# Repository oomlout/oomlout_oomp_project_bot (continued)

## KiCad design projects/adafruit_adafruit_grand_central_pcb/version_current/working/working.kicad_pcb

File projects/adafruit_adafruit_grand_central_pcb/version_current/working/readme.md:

# OOMP Project  
## Adafruit-Grand-Central-PCB  by adafruit  
  
oomp key: oomp_projects_flat_adafruit_adafruit_grand_central_pcb  
(snippet of original readme)  
  
-- Adafruit Grand Central M4 Express featuring the SAMD51 PCB  
  
<a href="http://www.adafruit.com/products/4064"><br/>  
Click here to purchase one from the Adafruit shop</a>  
  
PCB files for the Adafruit Grand Central M4 Express featuring the SAMD51. Format is EagleCAD schematic and board layout  
* https://www.adafruit.com/product/4064  
  
--- Description  
  
We're selling out fast but making more all the time! Sign up to be notified when it's in the store!  
  
Are you ready? Really ready? Cause here comes the **Adafruit Grand Central** featuring the **Microchip ATSAMD51**. This dev board is so big, it's not named after a Metro train, it's a whole freakin' station!  
  
This board is like a freight train, with its 120MHz Cortex M4 with floating point support. Your code will zig and zag and zoom, and with a bunch of extra peripherals for support, this will for sure be your favorite new chipset.  
  
The Grand Central is the first SAMD board that has enough pins to make it in the form of the Arduino Mega - with a massive number of pins, tons of analog inputs, dual DAC output, 8 MBytes of QSPI flash, SD card socket, and a NeoPixel.  
  
To start off our ATSAMD51 journey we are going large with the Mega shape and pinout you know and love. The front half has the same shape and pinout as our Metro's, so it is compatible with all our shields. It's got analog pins where you expect, and SPI/UART/I2C hardware support in the same spot as the Metro 328 and M0. But!  
  full source readme at [readme_src.md](readme_src.md)  
  
source repo at: [https://github.com/adafruit/Adafruit-Grand-Central-PCB](https://github.com/adafruit/Adafruit-Grand-Central-PCB)  
## Board  

## Schematic  

[schematic pdf](working_schematic.pdf)  
## Images

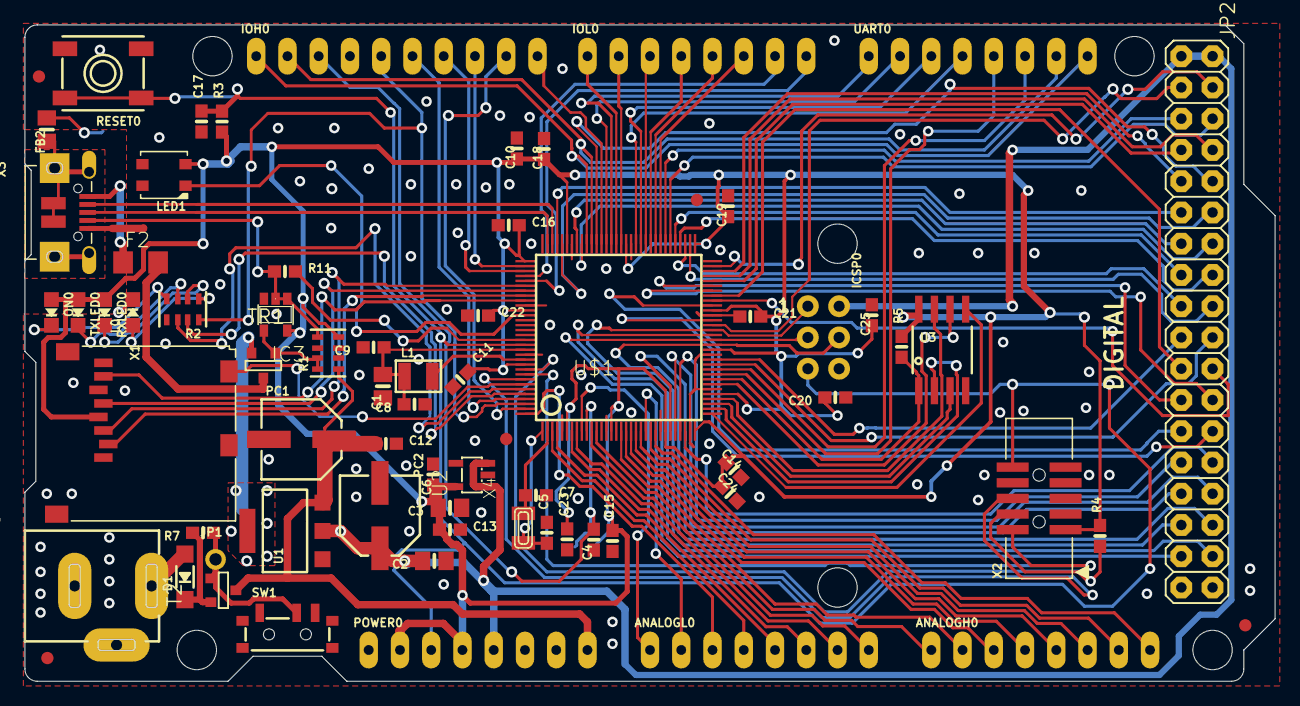
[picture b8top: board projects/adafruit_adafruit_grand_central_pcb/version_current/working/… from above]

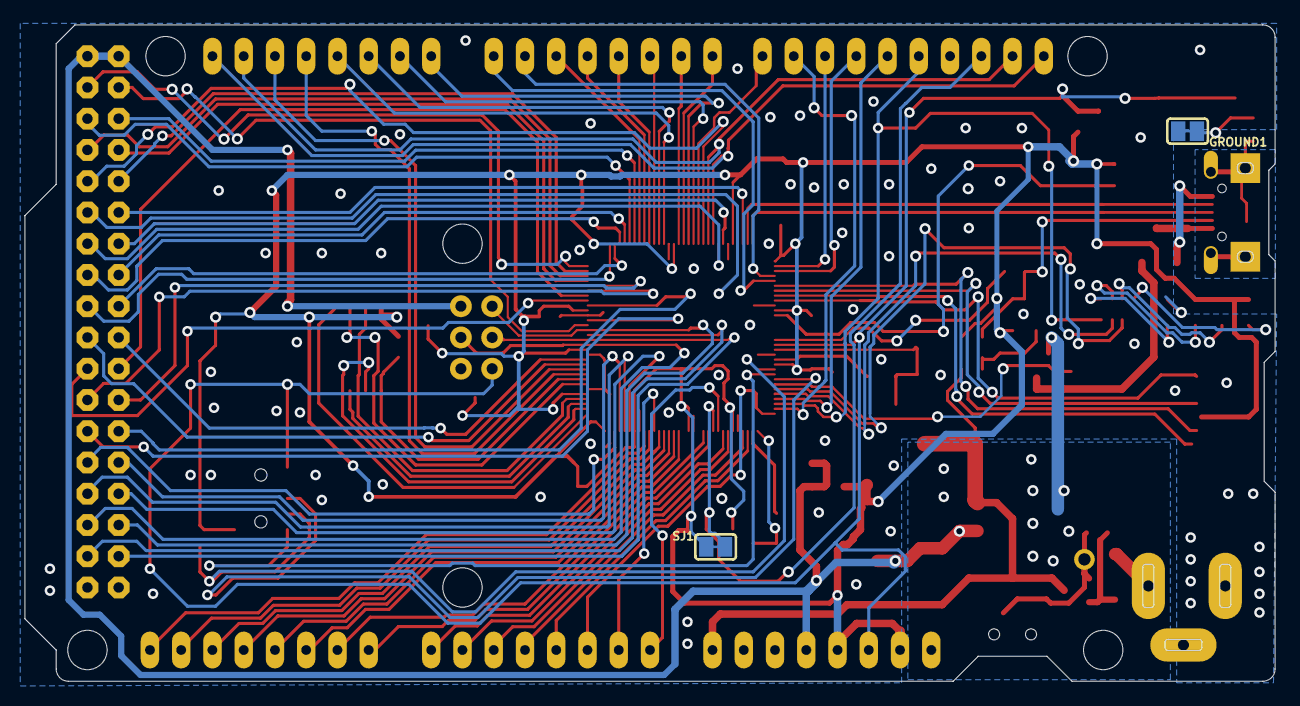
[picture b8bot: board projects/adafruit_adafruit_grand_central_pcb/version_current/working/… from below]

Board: 2 copper layers, 101.6 x 53.3 mm, 81 parts (3 on the bottom side), 113 nets.

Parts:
@HOLE0, @HOLE1, @HOLE2, @HOLE3, @HOLE4, @HOLE5: (no value)
ANALOGH0: 20610; 1X08_OVALWAVE
ANALOGL0: 20610; 1X08_OVALWAVE
C1, C2, C3: 10uF; 0805-NO
C4, C6, C8, C10, C11, C14, C15, C16, C18, C19, C20, C21, C22, C23, C24, C25: .1u; 0603-NO
C5, C7: 22pF; 0603-NO
C9: 1uF; 0603-NO
C12, C13, C17: 0.1uF; 0603-NO
D1: MBR120; SOD-123
F2: 500mA; R1206
FB2: FERRITE; 0805-NO
FD1, FD2, FD3, FD4, FD5: FIDUCIAL_1MM
GROUND1: SOLDERJUMPER_CLOSEDWIRE
IC3: 74LVC1G125D; SOT23-5
ICSP0: 3x2 M; 2X03_ROUND_70MIL
IOH0: 20611; 1X10_OVALWAVE
IOL0: 20610; 1X08_OVALWAVE
JP1: 1X01_ROUND
JP2: 2X18_THICKWAVE
L0: RED; CHIPLED_0805_NOOUTLINE
L1: 10uH; INDUCTOR_1007
LED1: WS2812B3535; LED3535
ON0: GREEN; CHIPLED_0805_NOOUTLINE
PC1: 47uF/25V; PANASONIC_D
PC2: 47uF+/6.3V+; PANASONIC_D
POWER0: 20610; 1X08_OVALWAVE
R1: 100K; RESPACK_4X0603
R2: 1K; RESPACK_4X0603
R3, R5, R7: 10K; 0603-NO
R4: 1K; 0603-NO
R11: 330R; 0603-NO
RESET0: EVQQ 6mm; EVQ-Q2_SMALLER
RXLED0: YELLOW; CHIPLED_0805_NOOUTLINE
SJ1: AREF_3V; SOLDERJUMPER_CLOSEDWIRE
SW1: SPDT_SMT_SSSS811101
T2: DMP3098L-7; SOT-23
TR1: DMP3098L-7; SOT-23
TXLED0: YELLOW; CHIPLED_0805_NOOUTLINE
U1: NCP1117ST50T3G; SOT223-R
U2: AP2112K-3.3; SOT23-DBV
U3: GD25Q64; SOIC8_208MIL
U$1: SAMD51PXXA; SQFP-S-14X14-128
U$23: GRANDCENTRAL_REVB-BOT
U$30: GRANDCENTRAL_REVB_TOP
UART0: 20610; 1X08_OVALWAVE
X1: microsd; MICROSD
X2: 2x5 0.05" SWD; 2X05_1.27MM_BOX_POSTS
X3: 20329; 4UCONN_20329_V2
X4: 32.768; XTAL3215
X5: 2.1mm; DCJACK_2MM_PTH

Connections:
3.3V: C3.2, C6.2, C10.2, C11.2, C13.1, C14.2, C15.2, C16.2, C18.2, C19.2, C20.2, C21.2, C22.2, C23.2, C24.2, C25.2, IC3.5, LED1.2, ON0.A, POWER0.2, POWER0.4, R1.4, R3.1, R4.2, R5.2, RXLED0.A, SJ1.1, TXLED0.A, U2.5, U3.8, U$1.6, U$1.15, U$1.26, U$1.32, U$1.37, U$1.46, U$1.54, U$1.65, U$1.79, U$1.91, U$1.97, U$1.107, U$1.118, X1.4, X2.1
+5V: C2.2, ICSP0.2, JP2.1, JP2.2, PC2.+, POWER0.5, TR1.2, U1.2, U1.4, U2.1, U2.3
A0: ANALOGL0.1, U$1.9
A1: ANALOGL0.2, U$1.22
A2: ANALOGL0.3, U$1.128
A3: ANALOGL0.4, U$1.3
A4: ANALOGL0.5, U$1.4
A5: ANALOGL0.6, U$1.7
A6: ANALOGL0.7, U$1.8
A7: ANALOGL0.8, U$1.11
A8: ANALOGH0.1, U$1.12
A9: ANALOGH0.2, U$1.17
A10: ANALOGH0.3, U$1.18
A11: ANALOGH0.4, U$1.19
A12: ANALOGH0.5, U$1.20
A13: ANALOGH0.6, U$1.21
A14: ANALOGH0.7, U$1.23
A15: ANALOGH0.8, U$1.24
AREF: C4.1, IOH0.3, SJ1.2, U$1.10
D0: IOL0.8, U$1.101
D1: IOL0.7, U$1.100
D2: IOL0.6, U$1.72
D3: IOL0.5, U$1.73
D4: IOL0.4, U$1.74
D5: IOL0.3, U$1.75
D6: IOL0.2, U$1.80
D7: IOL0.1, U$1.81
D8: IOH0.10, U$1.84
D9: IOH0.9, U$1.127
D10: IOH0.8, U$1.98
D11: IOH0.7, U$1.99
D12: IOH0.6, U$1.125
D13: IOH0.5, R2.8, U$1.126
D22: JP2.3, U$1.51
D23: JP2.4, U$1.63
D44: JP2.25, U$1.55
D45: JP2.26, U$1.52
D46: JP2.27, U$1.29
D47: JP2.28, U$1.30
D48: JP2.29, U$1.27
D49: JP2.30, U$1.28
D+: U$1.95, X3.D+
D-: U$1.94, X3.D-
FLASH_CS: R5.1, U3.1, U$1.40
FLASH_IO0: U3.5, U$1.33
FLASH_IO1: U3.2, U$1.34
FLASH_IO2: U3.3, U$1.35
FLASH_IO3: U3.7, U$1.36
FLASH_SCK: U3.6, U$1.39
GND: C1.2, C2.1, C3.1, C4.2, C5.2, C6.1, C7.2, C8.1, C9.2, C10.1, C11.1, C12.2, C13.2, C14.1, C15.1, C16.1, C17.1, C18.1, C19.1, C20.1, C21.1, C22.1, C23.1, C24.1, C25.1, GROUND1.2, IC3.3, ICSP0.6, IOH0.4, JP2.35, JP2.36, L0.C, LED1.4, PC1.-, PC2.-, POWER0.6, POWER0.7, R1.2, R2.5, RESET0.A, RESET0.A', SW1.A, U1.1, U2.2, U3.4, U$1.5, U$1.14, U$1.25, U$1.31, U$1.38, U$1.45, U$1.53, U$1.64, U$1.78, U$1.90, U$1.96, U$1.106, U$1.116, X1.6, X1.MT1, X1.MT2, X2.3, X2.5, X3.GND, X5.GND, X5.GNDBREAK
MISO: ICSP0.1, JP2.31, U$1.50
MOSI: ICSP0.4, JP2.32, U$1.47
unnamed: L0.A, R2.1
unnamed: FB2.1, GROUND1.1
unnamed: ON0.C, R2.4
unnamed: L1.P$2, U$1.117
unnamed: R2.2, RXLED0.C
unnamed: R2.3, TXLED0.C
unnamed: C5.1, U$1.1, X4.P$1
unnamed: IC3.1, IC3.2, R1.5, R11.1, X3.ID
unnamed: IC3.4, R1.7, R1.8, TR1.3
unnamed: C7.1, U$1.2, X4.P$2
unnamed: D1.C, R7.2, T2.2
NEOPIX: LED1.1, U$1.108
PCC_CLK: JP2.9, U$1.62
PCC_D0: JP2.18, U$1.66
PCC_D1: JP2.17, U$1.67
PCC_D2: JP2.16, U$1.68
PCC_D3: JP2.15, U$1.69
PCC_D4: JP2.14, U$1.88
PCC_D5: JP2.13, U$1.89
PCC_D6: JP2.12, U$1.92
PCC_D7: JP2.11, U$1.93
PCC_D8: JP2.20, U$1.43
PCC_D9: JP2.19, U$1.44
PCC_D10: JP2.22, U$1.56
PCC_D11: JP2.21, U$1.57
PCC_D12: JP2.24, U$1.58
PCC_D13: JP2.23, U$1.59
PCC_DEN1: JP2.7, U$1.60
PCC_DEN2: JP2.8, U$1.61
PCC_XCLK: JP2.10, U$1.85
PWRIN: D1.A, X5.PWR
PWR_SWITCH: JP1.1, R7.1, SW1.B, T2.3
RXLED: R2.7, U$1.124
SCK: ICSP0.3, JP2.33, U$1.48
SCL: IOH0.1, U$1.87, UART0.8
SCL_1: JP2.5, U$1.71
SDA: IOH0.2, U$1.86, UART0.7
SDA_1: JP2.6, U$1.70
SD_CD: U$1.122, X1.CD1
SD_CS: U$1.104, X1.2
SD_MISO: U$1.105, X1.7
SD_MOSI: U$1.102, X1.3
SD_SCK: U$1.103, X1.5
SS: JP2.34, U$1.49
SWCLK: R4.1, U$1.119, X2.4
SWDIO: U$1.120, X2.2
SWO: U$1.121, X2.6
TXLED: R2.6, U$1.123
UART1_RX: U$1.42, UART0.6
UART1_TX: U$1.41, UART0.5
UART2_RX: U$1.77, UART0.4
UART2_TX: U$1.76, UART0.3
UART3_RX: U$1.83, UART0.2
UART3_TX: U$1.82, UART0.1
USBVCC: F2.2, TR1.1
USB_HOSTEN: R11.2, U$1.113
USHIELD: FB2.2, X3.BASE@1, X3.BASE@2, X3.SPRT@1, X3.SPRT@2, X3.SPRT@3, X3.SPRT@4
VBUS: F2.1, X3.VBUS
VDDCORE: C1.1, C8.2, C9.1, L1.P$1, U$1.115
VIN: C12.1, PC1.+, POWER0.8, R1.1, T2.1, U1.3
~RESET: C17.2, ICSP0.5, POWER0.3, R3.2, RESET0.B, RESET0.B', U$1.114, X2.10
